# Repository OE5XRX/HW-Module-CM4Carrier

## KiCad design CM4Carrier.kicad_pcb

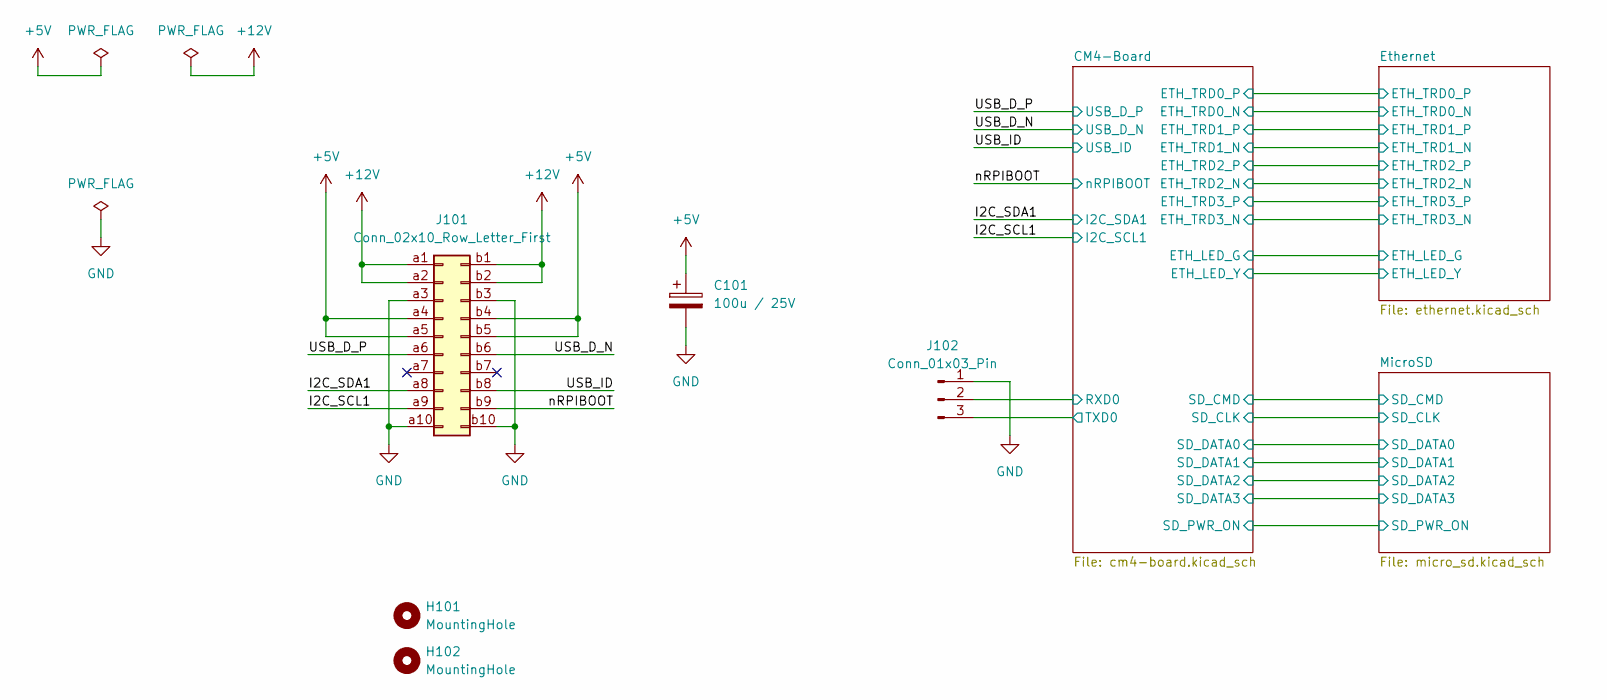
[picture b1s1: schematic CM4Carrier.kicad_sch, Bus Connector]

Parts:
C101: 100u / 25V; CP_EIA-7343-43_Kemet-X; LCSC C132558
H101, H102: MountingHole; MountingHole_3.2mm_M3
J101: Conn_02x10_Row_Letter_First; PCN10C-20S-2.54DS; MOUSER 798-PCN10C20S254DS72
J102: Conn_01x03_Pin; PinHeader_1x03_P2.54mm_Horizontal

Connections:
+5V: C101.1, J101.a4, J101.a5, J101.b4, J101.b5; also elsewhere on the board
+12V: J101.a1, J101.a2, J101.b1, J101.b2
/CM4-Board/RXD0: J102.2; also elsewhere on the board
/CM4-Board/TXD0: J102.3; also elsewhere on the board
/I2C_SCL1: J101.a9; also elsewhere on the board
/I2C_SDA1: J101.a8; also elsewhere on the board
/USB_D_N: J101.b6; also elsewhere on the board
/USB_D_P: J101.a6; also elsewhere on the board
/USB_ID: J101.b8; also elsewhere on the board
/nRPIBOOT: J101.b9; also elsewhere on the board
GND: C101.2, J101.a3, J101.a10, J101.b3, J101.b10, J102.1; also elsewhere on the board

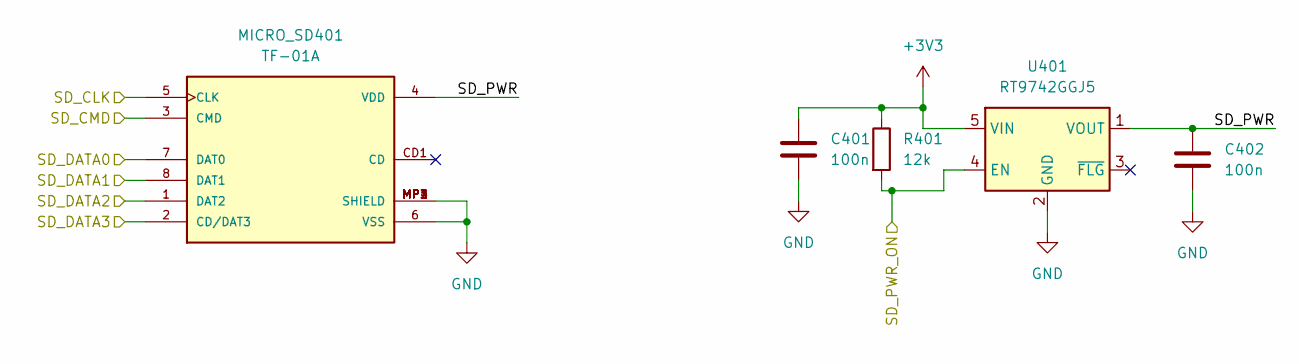
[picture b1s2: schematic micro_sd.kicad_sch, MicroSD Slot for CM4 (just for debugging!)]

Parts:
C401, C402: 100n; C_0805_2012Metric; LCSC C28233
MICRO_SD401: TF-01A; LCSC C91145
R401: 12k; R_0805_2012Metric; LCSC C17444
U401: RT9742GGJ5; TSOT-23-5; LCSC C250547

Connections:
+3V3: C401.1, R401.1, U401.5 (VIN); also elsewhere on the board
/CM4-Board/SD_CLK: MICRO_SD401.5 (CLK); also elsewhere on the board
/CM4-Board/SD_CMD: MICRO_SD401.3 (CMD); also elsewhere on the board
/CM4-Board/SD_DATA0: MICRO_SD401.7 (DAT0); also elsewhere on the board
/CM4-Board/SD_DATA1: MICRO_SD401.8 (DAT1); also elsewhere on the board
/CM4-Board/SD_DATA2: MICRO_SD401.1 (DAT2); also elsewhere on the board
/CM4-Board/SD_DATA3: MICRO_SD401.2 (CD/DAT3); also elsewhere on the board
/CM4-Board/SD_PWR_ON: R401.2, U401.4 (EN); also elsewhere on the board
/MicroSD/SD_PWR: C402.1, MICRO_SD401.4 (VDD), U401.1 (VOUT)
GND: C401.2, C402.2, MICRO_SD401.6 (VSS), MICRO_SD401.MP1 (SHIELD), MICRO_SD401.MP2 (SHIELD), MICRO_SD401.MP3 (SHIELD), MICRO_SD401.MP4 (SHIELD), U401.2 (GND); also elsewhere on the board

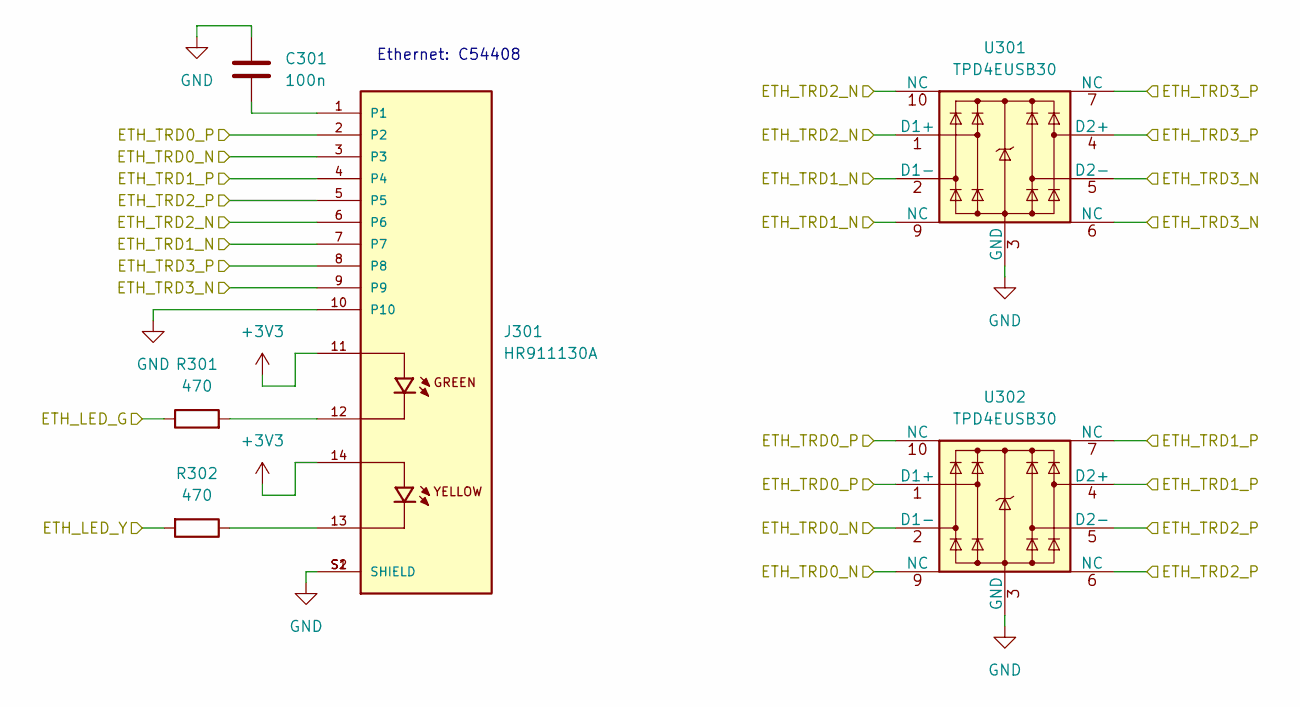
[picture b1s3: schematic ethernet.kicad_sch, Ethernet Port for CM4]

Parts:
C301: 100n; C_0805_2012Metric; LCSC C28233
J301: HR911130A; HANRUN_HR911130A; PARTREV A; LCSC C54408
R301, R302: 470; R_0805_2012Metric; LCSC C17710
U301, U302: TPD4EUSB30; USON-10_2.5x1.0mm_P0.5mm; LCSC C90627

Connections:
+3V3: J301.11, J301.14; also elsewhere on the board
/CM4-Board/ETH_LED_G: R301.1; also elsewhere on the board
/CM4-Board/ETH_LED_Y: R302.2; also elsewhere on the board
/CM4-Board/ETH_TRD0_N: J301.3, U302.2 (D1-), U302.9 (NC); also elsewhere on the board
/CM4-Board/ETH_TRD0_P: J301.2, U302.1 (D1+), U302.10 (NC); also elsewhere on the board
/CM4-Board/ETH_TRD1_N: J301.7, U301.2 (D1-), U301.9 (NC); also elsewhere on the board
/CM4-Board/ETH_TRD1_P: J301.4, U302.4 (D2+), U302.7 (NC); also elsewhere on the board
/CM4-Board/ETH_TRD2_N: J301.6, U301.1 (D1+), U301.10 (NC); also elsewhere on the board
/CM4-Board/ETH_TRD2_P: J301.5, U302.5 (D2-), U302.6 (NC); also elsewhere on the board
/CM4-Board/ETH_TRD3_N: J301.9, U301.5 (D2-), U301.6 (NC); also elsewhere on the board
/CM4-Board/ETH_TRD3_P: J301.8, U301.4 (D2+), U301.7 (NC); also elsewhere on the board
GND: C301.1, J301.10, J301.S1 (SHIELD), J301.S2 (SHIELD), U301.3 (GND), U301.8 (GND), U302.3 (GND), U302.8 (GND); also elsewhere on the board
unnamed: C301.2, J301.1
unnamed: J301.12, R301.2
unnamed: J301.13, R302.1

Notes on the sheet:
Ethernet: C54408

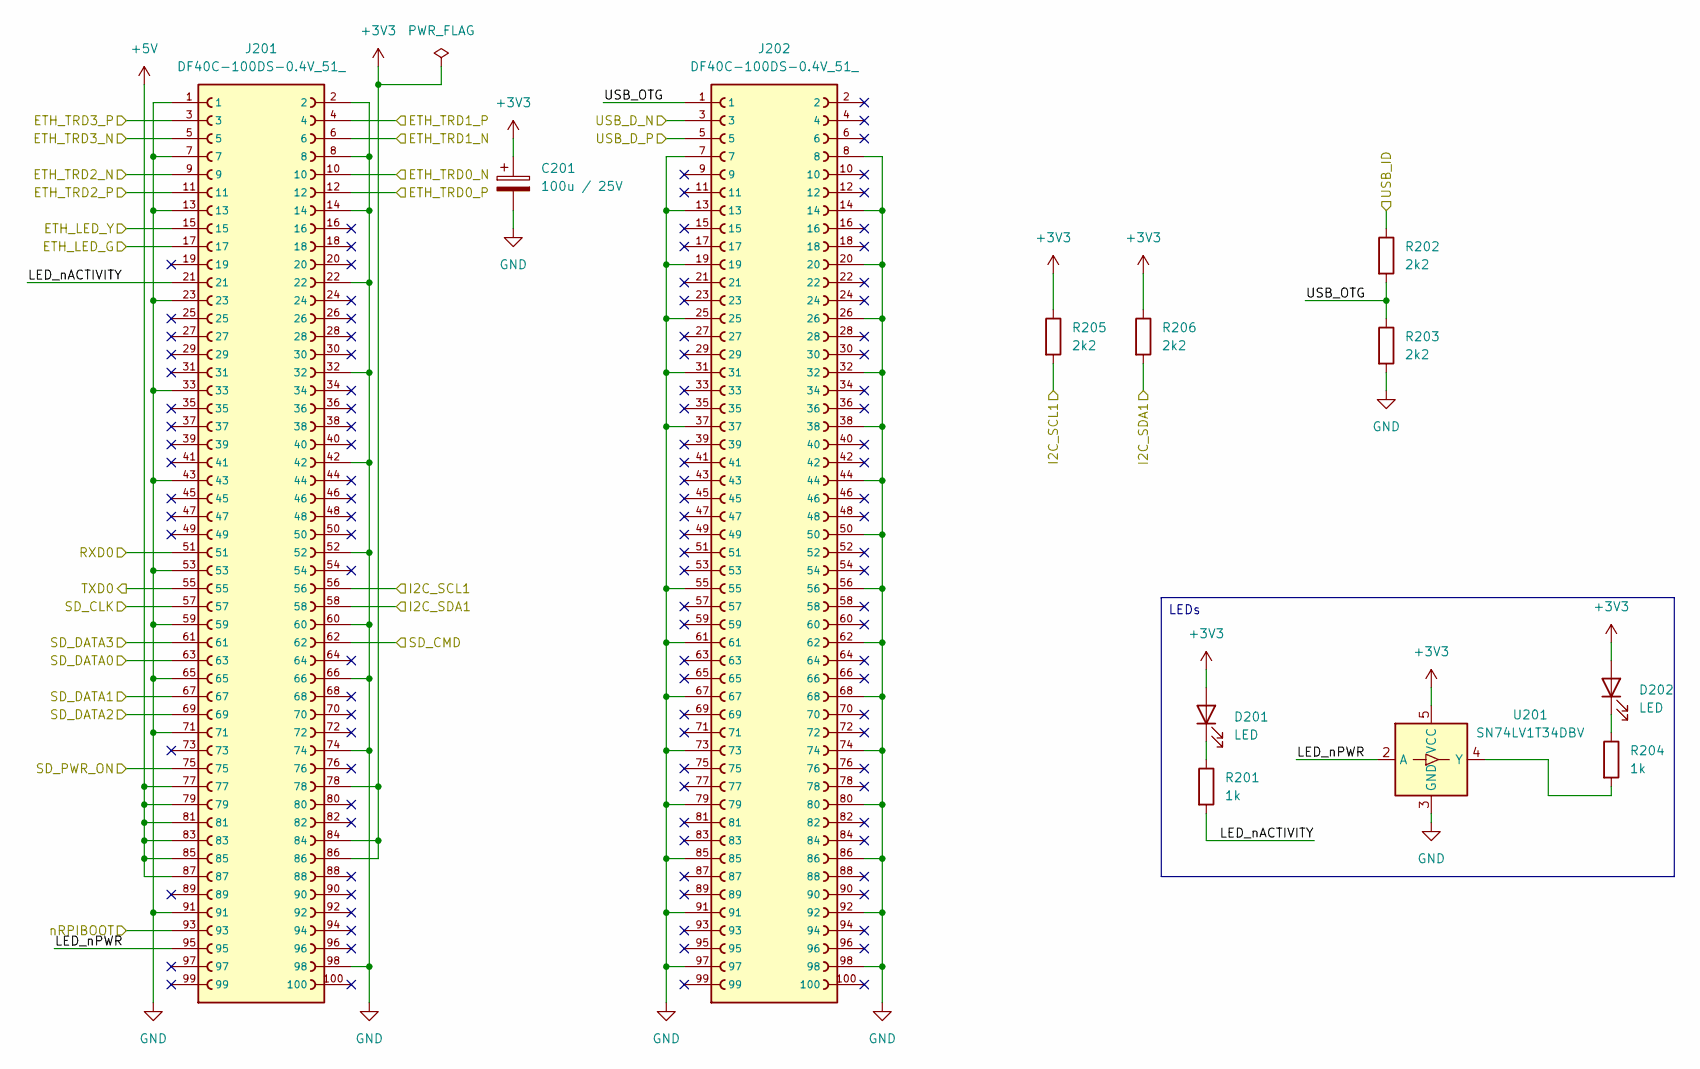
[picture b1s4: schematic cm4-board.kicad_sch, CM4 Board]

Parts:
C201: 100u / 25V; CP_EIA-7343-43_Kemet-X; LCSC C132558
D201, D202: LED; LED_0805_2012Metric; LCSC C84256
J201, J202: DF40C-100DS-0.4V_51_; HIROSE_DF40C-100DS-0.4V_51_; PARTREV Oct.1.2023; LCSC C597931
R201, R204: 1k; R_0805_2012Metric; LCSC C17513
R202, R203, R205, R206: 2k2; R_0805_2012Metric; LCSC C17520
U201: SN74LV1T34DBV; SOT-23-5; LCSC C100024

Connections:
+3V3: C201.1, D201.2 (A), D202.2 (A), J201.78, J201.84, J201.86, R205.1, R206.1, U201.5 (VCC); also elsewhere on the board
+5V: J201.77, J201.79, J201.81, J201.83, J201.85, J201.87; also elsewhere on the board
/CM4-Board/ETH_LED_G: J201.17; also elsewhere on the board
/CM4-Board/ETH_LED_Y: J201.15; also elsewhere on the board
/CM4-Board/ETH_TRD0_N: J201.10; also elsewhere on the board
/CM4-Board/ETH_TRD0_P: J201.12; also elsewhere on the board
/CM4-Board/ETH_TRD1_N: J201.6; also elsewhere on the board
/CM4-Board/ETH_TRD1_P: J201.4; also elsewhere on the board
/CM4-Board/ETH_TRD2_N: J201.9; also elsewhere on the board
/CM4-Board/ETH_TRD2_P: J201.11; also elsewhere on the board
/CM4-Board/ETH_TRD3_N: J201.5; also elsewhere on the board
/CM4-Board/ETH_TRD3_P: J201.3; also elsewhere on the board
/CM4-Board/LED_nACTIVITY: J201.21, R201.2
/CM4-Board/LED_nPWR: J201.95, U201.2 (A)
/CM4-Board/RXD0: J201.51; also elsewhere on the board
/CM4-Board/SD_CLK: J201.57; also elsewhere on the board
/CM4-Board/SD_CMD: J201.62; also elsewhere on the board
/CM4-Board/SD_DATA0: J201.63; also elsewhere on the board
/CM4-Board/SD_DATA1: J201.67; also elsewhere on the board
/CM4-Board/SD_DATA2: J201.69; also elsewhere on the board
/CM4-Board/SD_DATA3: J201.61; also elsewhere on the board
/CM4-Board/SD_PWR_ON: J201.75; also elsewhere on the board
/CM4-Board/TXD0: J201.55; also elsewhere on the board
/CM4-Board/USB_OTG: J202.1, R202.2, R203.1
/I2C_SCL1: J201.56, R205.2; also elsewhere on the board
/I2C_SDA1: J201.58, R206.2; also elsewhere on the board
/USB_D_N: J202.3; also elsewhere on the board
/USB_D_P: J202.5; also elsewhere on the board
/USB_ID: R202.1; also elsewhere on the board
/nRPIBOOT: J201.93; also elsewhere on the board
GND: C201.2, J201.1, J201.2, J201.7, J201.8, J201.13, J201.14, J201.22, J201.23, J201.32, J201.33, J201.42, J201.43, J201.52, J201.53, J201.59, J201.60, J201.65, J201.66, J201.71, J201.74, J201.91, J201.98, J202.7, J202.8, J202.13, J202.14, J202.19, J202.20, J202.25, J202.26, J202.31, J202.32, J202.37, J202.38, J202.44, J202.50, J202.55, J202.56, J202.61, J202.62, J202.67, J202.68, J202.73, J202.74, J202.79, J202.80, J202.85, J202.86, J202.91, J202.92, J202.97, J202.98, R203.2, U201.3 (GND); also elsewhere on the board
unnamed: D201.1 (K), R201.1
unnamed: D202.1 (K), R204.1
unnamed: R204.2, U201.4 (Y)

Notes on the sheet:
LEDs

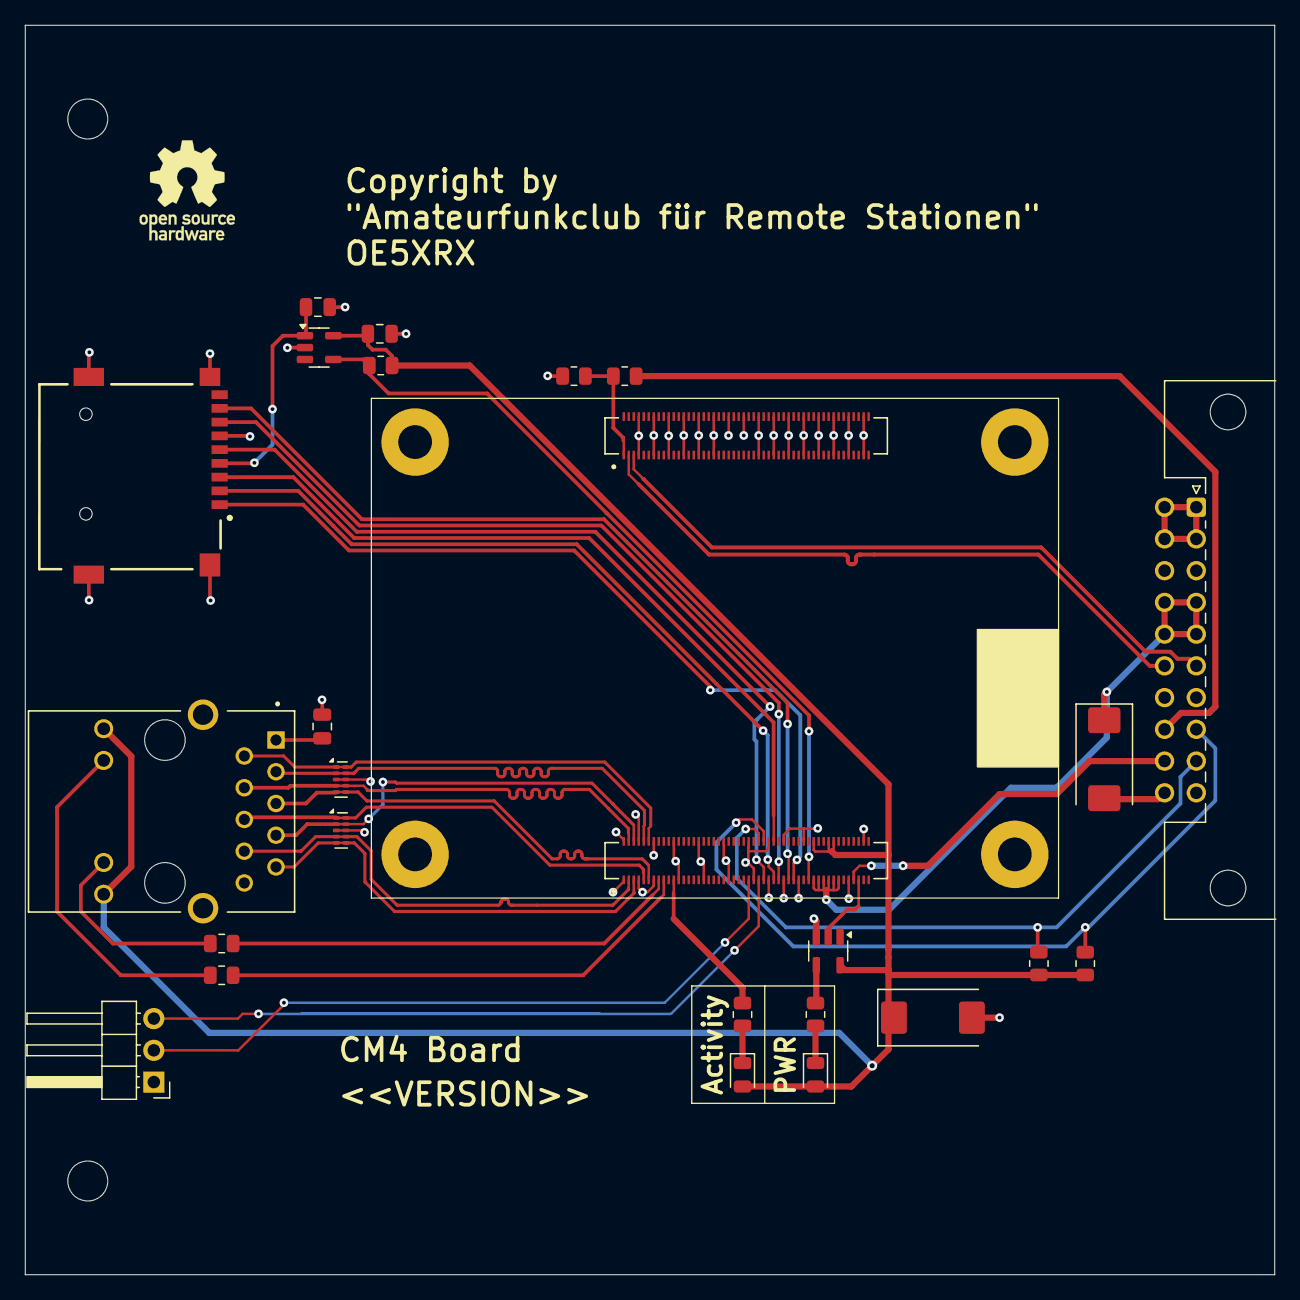
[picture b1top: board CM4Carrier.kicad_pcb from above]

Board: 4 copper layers, 100.0 x 100.0 mm, 28 parts (0 on the bottom side), 39 nets.

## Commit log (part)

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2025-08-28 setup project
2025-09-01 update gh pages generation
2026-05-12 refactor(ci): replace workflows with HW-Module-CI thin wrappers
2026-05-12 chore(ci): delete files now provided by HW-Module-CI
2026-05-12 feat(docs): migrate index.md to Jekyll Liquid for output paths
2026-05-12 chore: ignore CI-generated doc/_data/project.yml
2026-05-12 rename(kicad): main.kicad_* → CM4Carrier.kicad_*
2026-05-12 Deploying to gh-pages from @ OE5XRX/HW-Module-CM4Carrier@580c98fc0f9fd48bf3524a418f4030ede9c46d5c 🚀
2026-05-12 Initial gh-pages commit
2026-05-12 Deploying to gh-pages from @ OE5XRX/HW-Module-CM4Carrier@aeb54aefe455e349a8889f5acb7013ac1a5cecbd 🚀
2026-05-12 docs: rewrite CM4 Carrier index.md with full architecture overview
    Adds:
    - 1-sentence description front-matter
    - Übersicht highlighting Ethernet/SD/USB/I²C/UART/rpiboot roles
    - Mermaid block diagram showing CM4 + peripherals + bus interface
    - CM4 variant compatibility table (eMMC for production, lite for dev,
    non-Wifi only — confirmed with user)
2026-05-12 docs: correct rpiboot workflow — two manual jumpers required, not automatic
    Initial wording suggested the DeviceTester auto-pulls nRPIBOOT when the
    Carrier is inserted. Actually it's two manual jumpers on DeviceTester's
    4-pin Flash-Header J202:
    Pin 1: GND
    Pin 2: nRPIBOOT → short to Pin 1 for rpiboot mode
    Pin 3: USB_OTG_ID → short to Pin 1 for USB device mode
2026-05-12 fix(docs): USB_OTG_ID jumper goes to +5V not GND (rpiboot device-mode)
    User-correction: Pin 4 of the DeviceTester's J202 Flash-Header is +5V_A
    and sits right next to USB_OTG_ID (Pin 3) — that's not a coincidence;
    the layout exists to enable jumping Pin 3↔4 to pull USB_OTG_ID HIGH.
    Pulling USB_OTG_ID HIGH puts the CM4's USB-OTG port in DEVICE mode (PC
    becomes host, CM4 becomes peripheral) — required for rpiboot to talk
    to the CM4. Pulling it to GND would force HOST mode, which is wrong
2026-05-12 Deploying to gh-pages from @ OE5XRX/HW-Module-CM4Carrier@8b3b603463d66f7d5d0799750094fccb0213fd9b 🚀
2026-05-13 fix(docs): J101 ist PCN10C-20S-2.54DS (weibliche Buchse), nicht PCN10-20P-2.54DSA
    Verifiziert gegen CM4Carrier.kicad_pcb Footprint 'PRJ:PCN10C-20S-2.54DS'.
    PCN10-20P-2.54DSA ist der MÄNNLICHE Pin-Header auf dem BusBoard; auf der
    Consumer-Seite (CM4Carrier, FM Transceiver etc.) sitzt die WEIBLICHE
    Buchsen-Variante PCN10C-20S-2.54DS.
    Gleicher Fehler wurde auf der FM-Doku PR #14 via Copilot-Review gefunden.
2026-05-13 fix(docs): adressiere 4 weitere Copilot-Findings (RGMII/TPD4EUSB30/Boot-Order/Unicode)
    Copilot-Review hatte auf PR #4 vier valide Findings hinterlassen, die nun
    in dieser bereits offenen PR mit-adressiert werden:
    1. Mermaid-Beschriftung 'RGMII' zwischen CM4 und RJ45 war falsch. CM4
    hat den Ethernet-PHY intern; vom Chip zum RJ45 laufen die 4 MDI-
    Twisted-Pair-Differenzpaare (ETH_TRD0/1/2/3_P/N). RGMII wäre MAC↔PHY
    (intern im CM4). Beschriftung korrigiert auf 'MDI (4× TRD)' und die
2026-05-13 Deploying to gh-pages from @ OE5XRX/HW-Module-CM4Carrier@c2e082ac0e0863d0e8268c624a08d2215375bf9e 🚀
2026-05-15 Deploying to gh-pages from @ OE5XRX/HW-Module-CM4Carrier@146843e85249ff1d8463625cc417dff18ba55c7f 🚀
2026-05-15 Deploying to gh-pages from @ OE5XRX/HW-Module-CM4Carrier@9fa4b6715b59352daba81f308fd1c1465fd3cd9e 🚀

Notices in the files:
CM4Carrier.kicad_pcb:
Copyright by
{dblquote}Amateurfunkclub für Remote Stationen{dblquote}
